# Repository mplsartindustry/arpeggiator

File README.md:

# arpeggiator
Eurorack MIDI to CV arpeggiator

##### Panel

##### PCB

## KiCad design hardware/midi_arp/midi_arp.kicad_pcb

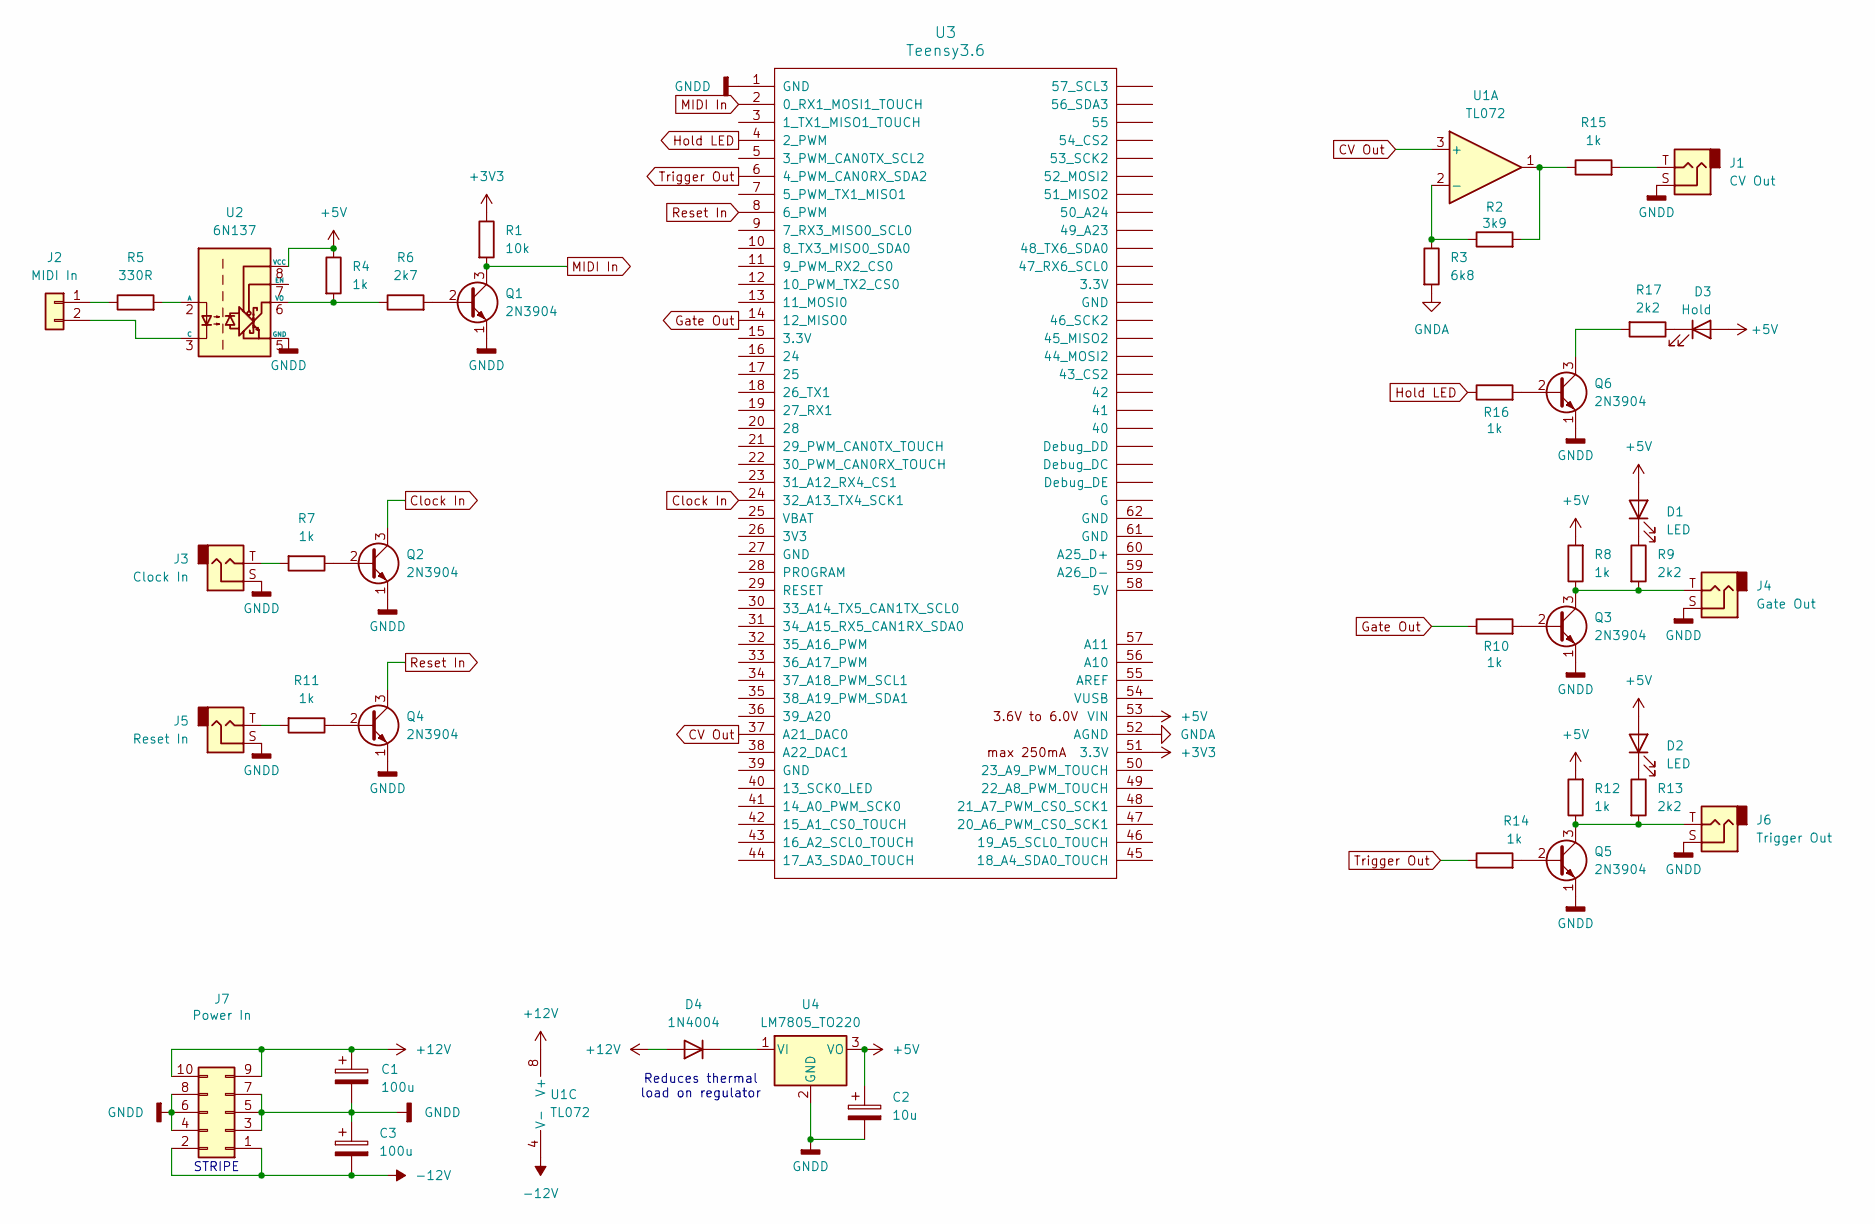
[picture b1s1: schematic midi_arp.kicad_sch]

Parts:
C1, C3: 100u; CP_Radial_D6.3mm_P2.50mm
C2: 10u; CP_Radial_D5.0mm_P2.00mm
D1, D2: LED; LED_D3.0mm
D3: Hold; LED_D3.0mm
D4: 1N4004; D_DO-41_SOD81_P7.62mm_Horizontal
J1: CV Out; Jack_3.5mm_QingPu_WQP-PJ398SM_Vertical_CircularHoles
J2: MIDI In; PinHeader_1x02_P2.54mm_Vertical
J3: Clock In; Jack_3.5mm_QingPu_WQP-PJ398SM_Vertical_CircularHoles
J4: Gate Out; Jack_3.5mm_QingPu_WQP-PJ398SM_Vertical_CircularHoles
J5: Reset In; Jack_3.5mm_QingPu_WQP-PJ398SM_Vertical_CircularHoles
J6: Trigger Out; Jack_3.5mm_QingPu_WQP-PJ398SM_Vertical_CircularHoles
J7: Power In; IDC-Header_2x05_P2.54mm_Vertical
Q1, Q2, Q3, Q4, Q5, Q6: 2N3904; TO-92_Inline
R1: 10k; R_Axial_DIN0207_L6.3mm_D2.5mm_P7.62mm_Horizontal
R2: 3k9; R_Axial_DIN0207_L6.3mm_D2.5mm_P7.62mm_Horizontal
R3: 6k8; R_Axial_DIN0207_L6.3mm_D2.5mm_P7.62mm_Horizontal
R4, R7, R8, R10, R11, R12, R14, R15, R16: 1k; R_Axial_DIN0207_L6.3mm_D2.5mm_P7.62mm_Horizontal
R5: 330R; R_Axial_DIN0207_L6.3mm_D2.5mm_P7.62mm_Horizontal
R6: 2k7; R_Axial_DIN0207_L6.3mm_D2.5mm_P7.62mm_Horizontal
R9, R13, R17: 2k2; R_Axial_DIN0207_L6.3mm_D2.5mm_P7.62mm_Horizontal
U1: TL072; DIP-8_W7.62mm_Socket
U2: 6N137; DIP-8_W7.62mm
U3: Teensy3.6; Teensy35_36
U4: LM7805_TO220; TO-220-3_Vertical

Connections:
+3V3: R1.1, U3.51 (3.3V)
+5V: C2.1, D1.2 (A), D2.2 (A), D3.2 (A), R4.1, R8.2, R12.2, U2.8 (VCC), U3.53 (VIN), U4.3 (VO)
+12V: C1.1, D4.2 (A), J7.9, J7.10, U1.8 (V+)
-12V: C3.2, J7.1, J7.2, U1.4 (V-)
CV Out: U1.3 (+), U3.37 (A21_DAC0)
Clock In: Q2.3 (C), U3.24 (32_A13_TX4_SCK1)
GNDA: R3.2, U3.52 (AGND)
GNDD: C1.2, C2.2, C3.1, J1.S, J3.S, J4.S, J5.S, J6.S, J7.3, J7.4, J7.5, J7.6, J7.7, J7.8, Q1.1 (E), Q2.1 (E), Q3.1 (E), Q4.1 (E), Q5.1 (E), Q6.1 (E), U2.5 (GND), U3.1 (GND), U4.2 (GND)
Gate Out: R10.1, U3.14 (12_MISO0)
Hold LED: R16.1, U3.4 (2_PWM)
MIDI In: Q1.3 (C), R1.2, U3.2 (0_RX1_MOSI1_TOUCH)
unnamed: D1.1 (K), R9.1
unnamed: D2.1 (K), R13.1
unnamed: D3.1 (K), R17.1
unnamed: D4.1 (K), U4.1 (VI)
unnamed: J1.T, R15.2
unnamed: J2.1, R5.1
unnamed: J2.2, U2.3 (C)
unnamed: J3.T, R7.2
unnamed: J5.T, R11.2
unnamed: Q1.2 (B), R6.2
unnamed: Q2.2 (B), R7.1
unnamed: Q3.2 (B), R10.2
unnamed: J4.T, Q3.3 (C), R8.1, R9.2
unnamed: Q4.2 (B), R11.1
unnamed: Q5.2 (B), R14.2
unnamed: J6.T, Q5.3 (C), R12.1, R13.2
unnamed: Q6.2 (B), R16.2
unnamed: Q6.3 (C), R17.2
unnamed: R2.2, R15.1, U1.1
unnamed: R2.1, R3.1, U1.2 (-)
unnamed: R5.2, U2.2 (A)
unnamed: R4.2, R6.1, U2.6 (VO)
Reset In: Q4.3 (C), U3.8 (6_PWM)
Trigger Out: R14.1, U3.6 (4_PWM_CAN0RX_SDA2)

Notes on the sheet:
STRIPE
Reduces thermal load on regulator

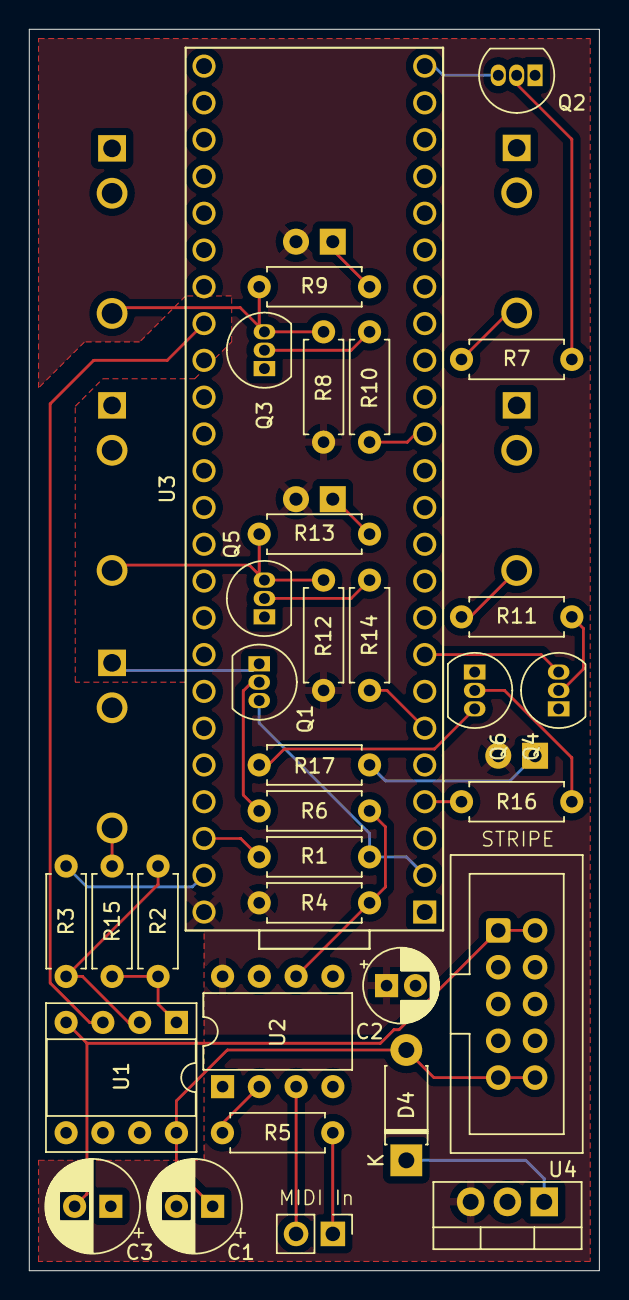
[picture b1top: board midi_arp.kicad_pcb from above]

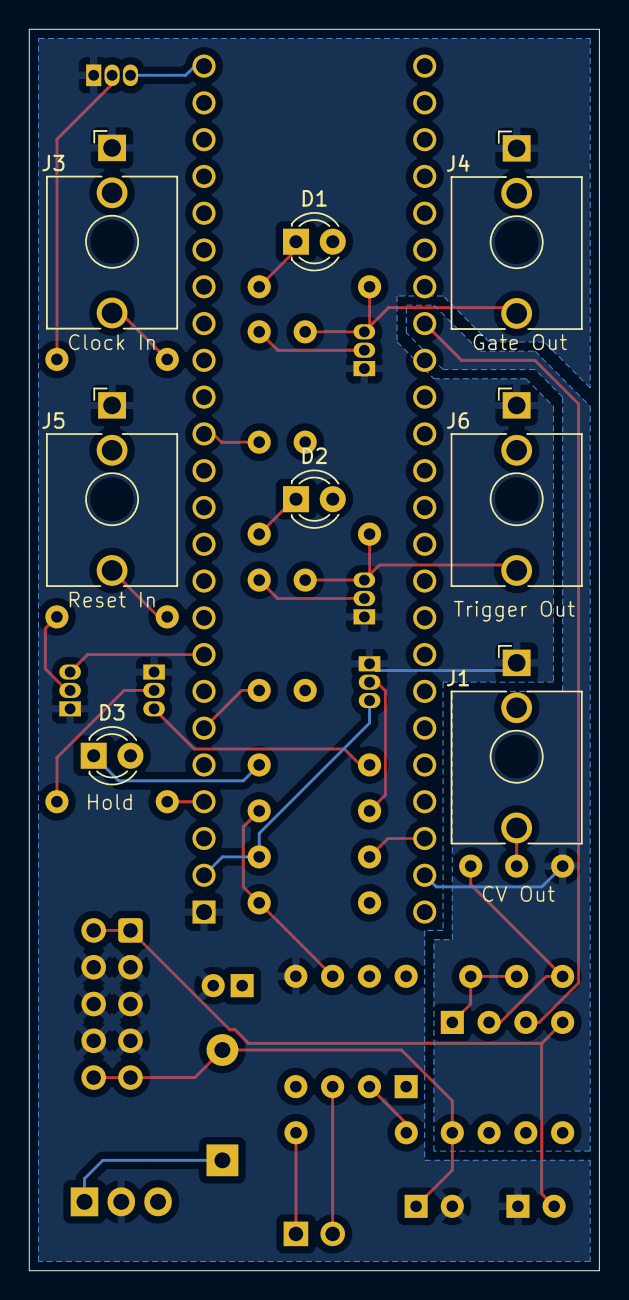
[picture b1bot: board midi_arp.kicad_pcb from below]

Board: 2 copper layers, 39.4 x 85.7 mm, 41 parts (8 on the bottom side), 35 nets.

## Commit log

2024-09-01 add license
2024-09-01 Add all the things
2024-09-01 Add hold mode
2024-09-01 add license header
2024-09-01 Refactor and add ordered mode
2024-09-02 fix up license header
2024-09-15 Add images
2024-09-15 Add images to README
2024-09-15 Flip images the right way up
2024-10-13 Fix off by one errors
